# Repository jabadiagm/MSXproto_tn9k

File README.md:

# MSXproto_tn9k
Placa de prototipado para cartucho MSX y Tang Nano 9K

Placa de prototipo para conectar una Tang Nano 9K a una ranura de cartucho MSX. Se incluyen adaptadores de nivel de 5V a 3.3V para los pines de salida digitales del cartucho.

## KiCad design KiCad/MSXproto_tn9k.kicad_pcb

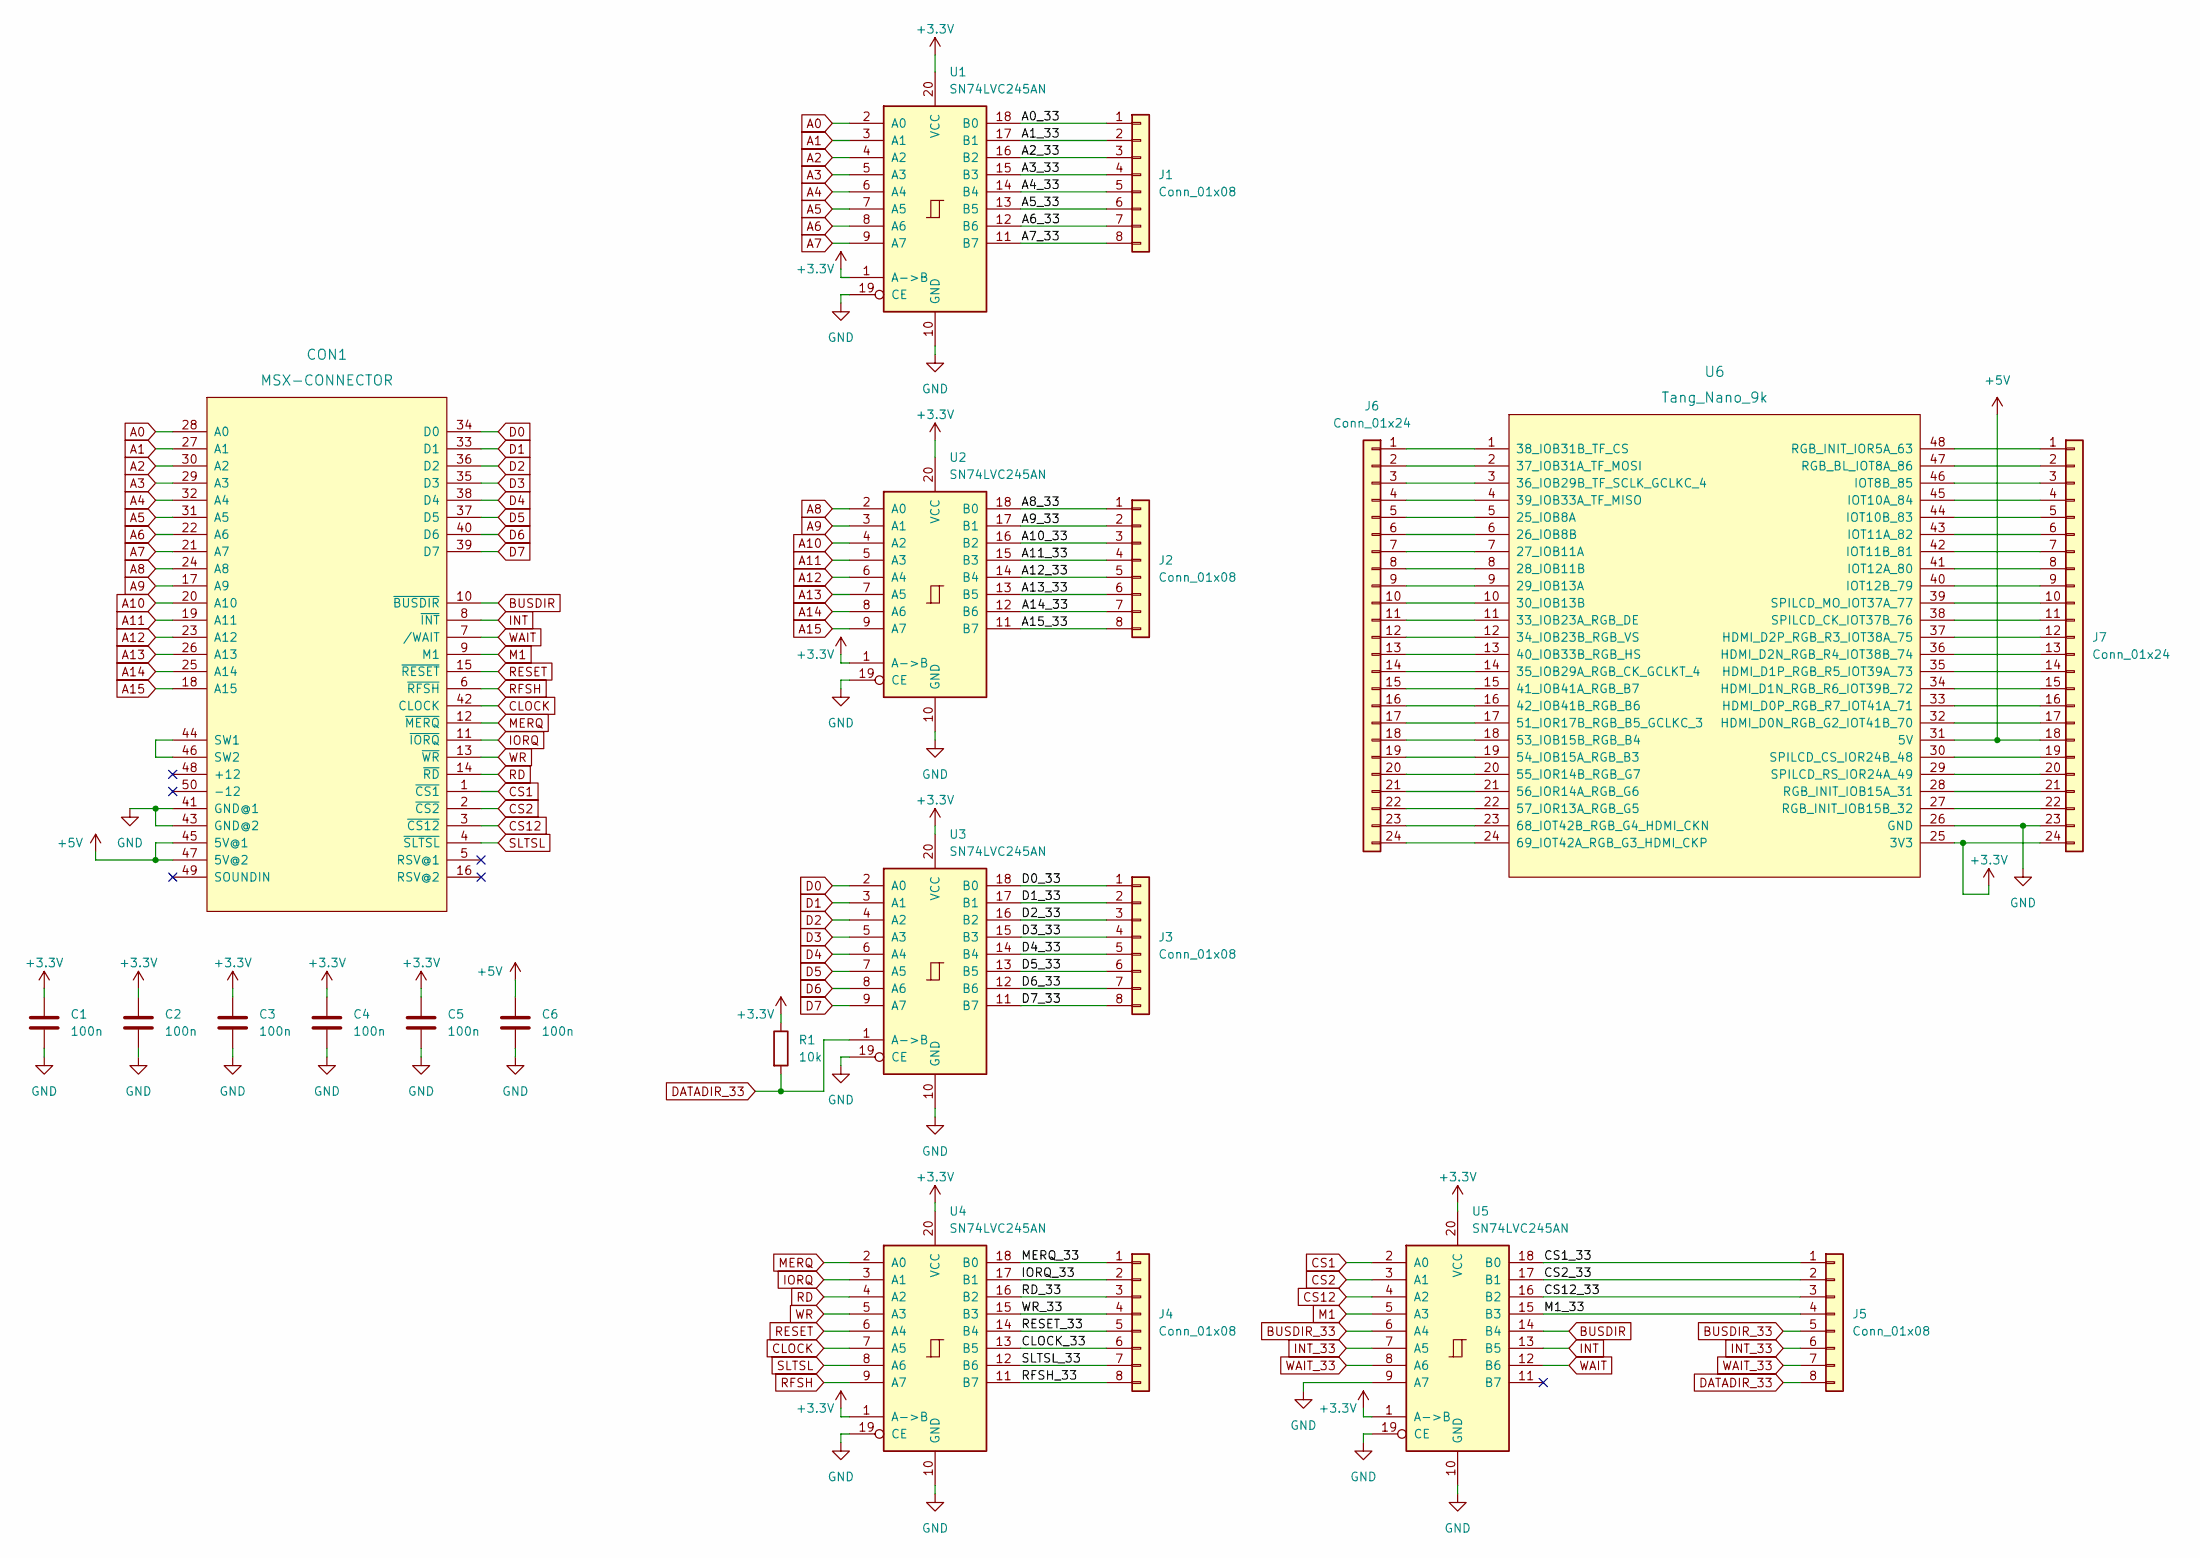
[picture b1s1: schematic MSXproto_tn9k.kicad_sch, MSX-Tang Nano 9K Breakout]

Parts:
C1, C2, C3, C4, C5, C6: 100n; C_Disc_D4.3mm_W1.9mm_P5.00mm
CON1: MSX-CONNECTOR; CARTRIDGE_MSX_XL
J1, J2, J3, J4, J5: Conn_01x08; PinSocket_1x08_P2.54mm_Vertical
J6, J7: Conn_01x24; PinSocket_1x24_P2.54mm_Vertical
R1: 10k; R_Axial_DIN0207_L6.3mm_D2.5mm_P7.62mm_Horizontal
U1, U2, U3, U4, U5: SN74LVC245AN; DIP-20_W7.62mm
U6: Tang_Nano_9k

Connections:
+3.3V: C1.1, C2.1, C3.1, C4.1, C5.1, J7.24, R1.1, U1.1 (A->B), U1.20 (VCC), U2.1 (A->B), U2.20 (VCC), U3.20 (VCC), U4.1 (A->B), U4.20 (VCC), U5.1 (A->B), U5.20 (VCC), U6.25 (3V3)
+5V: C6.1, CON1.45 (5V@1), CON1.47 (5V@2), J7.18, U6.31 (5V)
/A0_33: J1.1, U1.18 (B0)
/A1_33: J1.2, U1.17 (B1)
/A2_33: J1.3, U1.16 (B2)
/A3_33: J1.4, U1.15 (B3)
/A4_33: J1.5, U1.14 (B4)
/A5_33: J1.6, U1.13 (B5)
/A6_33: J1.7, U1.12 (B6)
/A7_33: J1.8, U1.11 (B7)
/A8_33: J2.1, U2.18 (B0)
/A9_33: J2.2, U2.17 (B1)
/A10_33: J2.3, U2.16 (B2)
/A11_33: J2.4, U2.15 (B3)
/A12_33: J2.5, U2.14 (B4)
/A13_33: J2.6, U2.13 (B5)
/A14_33: J2.7, U2.12 (B6)
/A15_33: J2.8, U2.11 (B7)
/CLOCK_33: J4.6, U4.13 (B5)
/CS1_33: J5.1, U5.18 (B0)
/CS2_33: J5.2, U5.17 (B1)
/CS12_33: J5.3, U5.16 (B2)
/D0_33: J3.1, U3.18 (B0)
/D1_33: J3.2, U3.17 (B1)
/D2_33: J3.3, U3.16 (B2)
/D3_33: J3.4, U3.15 (B3)
/D4_33: J3.5, U3.14 (B4)
/D5_33: J3.6, U3.13 (B5)
/D6_33: J3.7, U3.12 (B6)
/D7_33: J3.8, U3.11 (B7)
/IORQ_33: J4.2, U4.17 (B1)
/M1_33: J5.4, U5.15 (B3)
/MERQ_33: J4.1, U4.18 (B0)
/RD_33: J4.3, U4.16 (B2)
/RESET_33: J4.5, U4.14 (B4)
/RFSH_33: J4.8, U4.11 (B7)
/SLTSL_33: J4.7, U4.12 (B6)
/WR_33: J4.4, U4.15 (B3)
A0: CON1.28 (A0), U1.2 (A0)
A1: CON1.27 (A1), U1.3 (A1)
A2: CON1.30 (A2), U1.4 (A2)
A3: CON1.29 (A3), U1.5 (A3)
A4: CON1.32 (A4), U1.6 (A4)
A5: CON1.31 (A5), U1.7 (A5)
A6: CON1.22 (A6), U1.8 (A6)
A7: CON1.21 (A7), U1.9 (A7)
A8: CON1.24 (A8), U2.2 (A0)
A9: CON1.17 (A9), U2.3 (A1)
A10: CON1.20 (A10), U2.4 (A2)
A11: CON1.19 (A11), U2.5 (A3)
A12: CON1.23 (A12), U2.6 (A4)
A13: CON1.26 (A13), U2.7 (A5)
A14: CON1.25 (A14), U2.8 (A6)
A15: CON1.18 (A15), U2.9 (A7)
BUSDIR: CON1.10 (~BUSDIR), U5.14 (B4)
BUSDIR_33: J5.5, U5.6 (A4)
CLOCK: CON1.42 (CLOCK), U4.7 (A5)
CS1: CON1.1 (~CS1), U5.2 (A0)
CS2: CON1.2 (~CS2), U5.3 (A1)
CS12: CON1.3 (~CS12), U5.4 (A2)
D0: CON1.34 (D0), U3.2 (A0)
D1: CON1.33 (D1), U3.3 (A1)
D2: CON1.36 (D2), U3.4 (A2)
D3: CON1.35 (D3), U3.5 (A3)
D4: CON1.38 (D4), U3.6 (A4)
D5: CON1.37 (D5), U3.7 (A5)
D6: CON1.40 (D6), U3.8 (A6)
D7: CON1.39 (D7), U3.9 (A7)
DATADIR_33: J5.8, R1.2, U3.1 (A->B)
GND: C1.2, C2.2, C3.2, C4.2, C5.2, C6.2, CON1.41 (GND@1), CON1.43 (GND@2), J7.23, U1.10 (GND), U1.19 (CE), U2.10 (GND), U2.19 (CE), U3.10 (GND), U3.19 (CE), U4.10 (GND), U4.19 (CE), U5.9 (A7), U5.10 (GND), U5.19 (CE), U6.26 (GND)
INT: CON1.8 (~INT), U5.13 (B5)
INT_33: J5.6, U5.7 (A5)
IORQ: CON1.11 (~IORQ), U4.3 (A1)
M1: CON1.9 (M1), U5.5 (A3)
MERQ: CON1.12 (~MERQ), U4.2 (A0)
unnamed: CON1.44 (SW1), CON1.46 (SW2)
unnamed: J6.1, U6.1 (38_IOB31B_TF_CS)
unnamed: J6.2, U6.2 (37_IOB31A_TF_MOSI)
unnamed: J6.3, U6.3 (36_IOB29B_TF_SCLK_GCLKC_4)
unnamed: J6.4, U6.4 (39_IOB33A_TF_MISO)
unnamed: J6.5, U6.5 (25_IOB8A)
unnamed: J6.6, U6.6 (26_IOB8B)
unnamed: J6.7, U6.7 (27_IOB11A)
unnamed: J6.8, U6.8 (28_IOB11B)
unnamed: J6.9, U6.9 (29_IOB13A)
unnamed: J6.10, U6.10 (30_IOB13B)
unnamed: J6.11, U6.11 (33_IOB23A_RGB_DE)
unnamed: J6.12, U6.12 (34_IOB23B_RGB_VS)
unnamed: J6.13, U6.13 (40_IOB33B_RGB_HS)
unnamed: J6.14, U6.14 (35_IOB29A_RGB_CK_GCLKT_4)
unnamed: J6.15, U6.15 (41_IOB41A_RGB_B7)
unnamed: J6.16, U6.16 (42_IOB41B_RGB_B6)
unnamed: J6.17, U6.17 (51_IOR17B_RGB_B5_GCLKC_3)
unnamed: J6.18, U6.18 (53_IOB15B_RGB_B4)
unnamed: J6.19, U6.19 (54_IOB15A_RGB_B3)
unnamed: J6.20, U6.20 (55_IOR14B_RGB_G7)
unnamed: J6.21, U6.21 (56_IOR14A_RGB_G6)
unnamed: J6.22, U6.22 (57_IOR13A_RGB_G5)
unnamed: J6.23, U6.23 (68_IOT42B_RGB_G4_HDMI_CKN)
unnamed: J6.24, U6.24 (69_IOT42A_RGB_G3_HDMI_CKP)
unnamed: J7.22, U6.27 (RGB_INIT_IOB15B_32)
unnamed: J7.21, U6.28 (RGB_INIT_IOB15A_31)
unnamed: J7.20, U6.29 (SPILCD_RS_IOR24A_49)
unnamed: J7.19, U6.30 (SPILCD_CS_IOR24B_48)
unnamed: J7.17, U6.32 (HDMI_D0N_RGB_G2_IOT41B_70)
unnamed: J7.16, U6.33 (HDMI_D0P_RGB_R7_IOT41A_71)
unnamed: J7.15, U6.34 (HDMI_D1N_RGB_R6_IOT39B_72)
unnamed: J7.14, U6.35 (HDMI_D1P_RGB_R5_IOT39A_73)
unnamed: J7.13, U6.36 (HDMI_D2N_RGB_R4_IOT38B_74)
unnamed: J7.12, U6.37 (HDMI_D2P_RGB_R3_IOT38A_75)
unnamed: J7.11, U6.38 (SPILCD_CK_IOT37B_76)
unnamed: J7.10, U6.39 (SPILCD_MO_IOT37A_77)
unnamed: J7.9, U6.40 (IOT12B_79)
unnamed: J7.8, U6.41 (IOT12A_80)
unnamed: J7.7, U6.42 (IOT11B_81)
unnamed: J7.6, U6.43 (IOT11A_82)
unnamed: J7.5, U6.44 (IOT10B_83)
unnamed: J7.4, U6.45 (IOT10A_84)
unnamed: J7.3, U6.46 (IOT8B_85)
unnamed: J7.2, U6.47 (RGB_BL_IOT8A_86)
unnamed: J7.1, U6.48 (RGB_INIT_IOR5A_63)
RD: CON1.14 (~RD), U4.4 (A2)
RESET: CON1.15 (~RESET), U4.6 (A4)
RFSH: CON1.6 (~RFSH), U4.9 (A7)
SLTSL: CON1.4 (~SLTSL), U4.8 (A6)
WAIT: CON1.7 (/WAIT), U5.12 (B6)
WAIT_33: J5.7, U5.8 (A6)
WR: CON1.13 (~WR), U4.5 (A3)

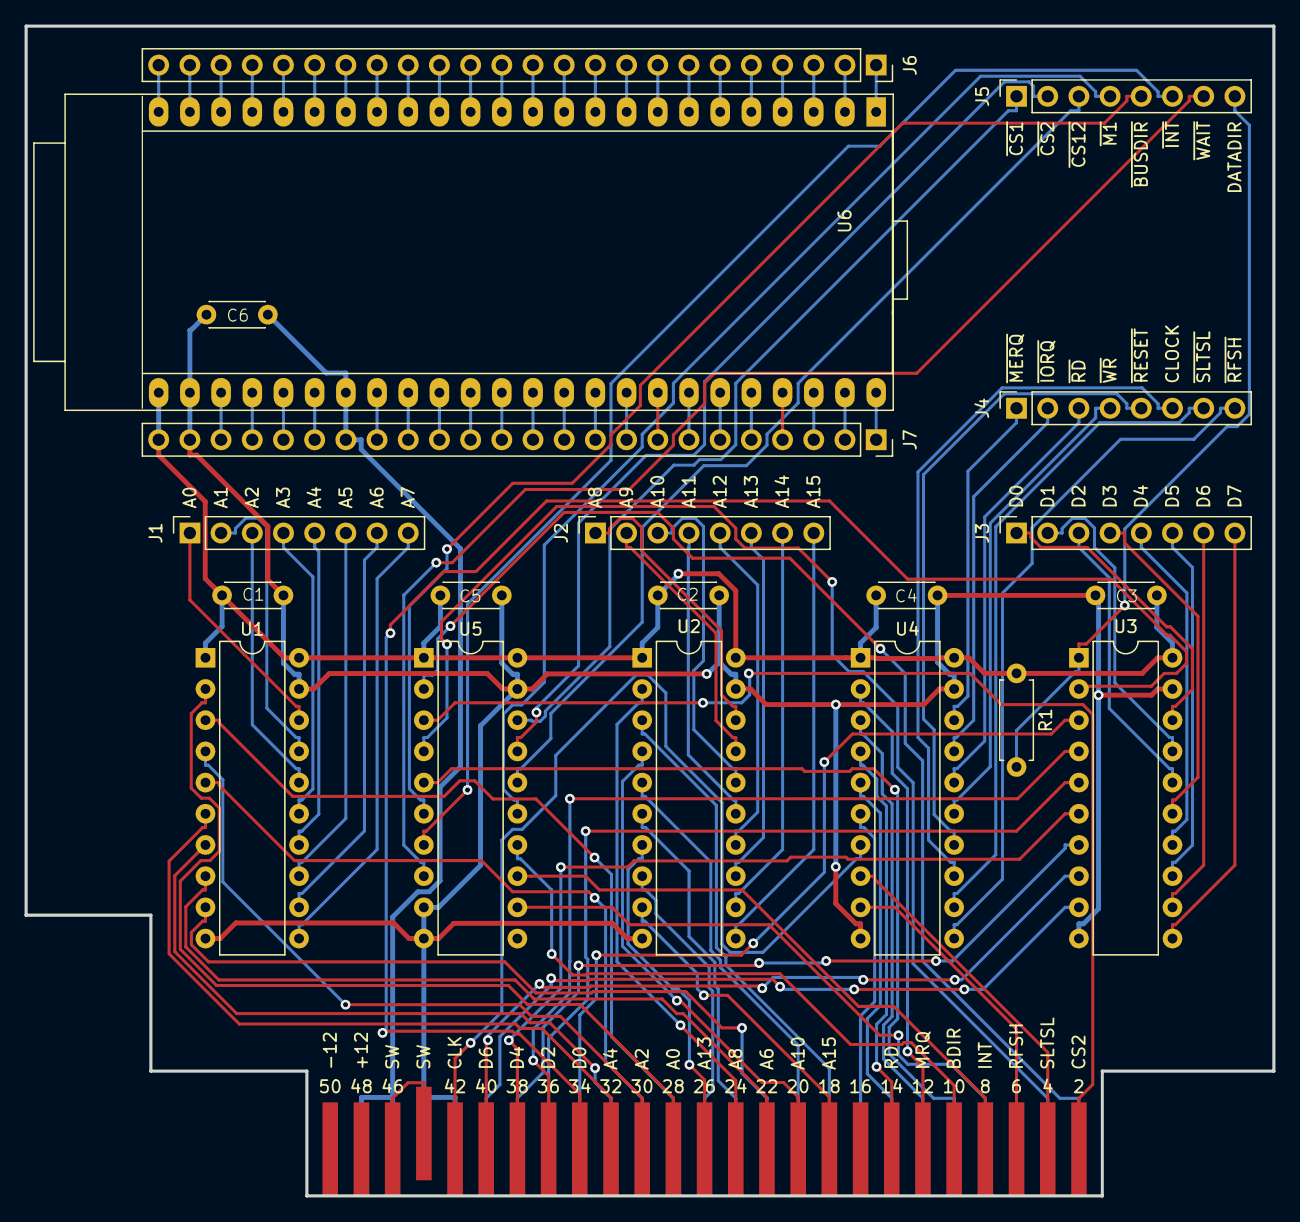
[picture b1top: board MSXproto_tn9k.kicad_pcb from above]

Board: 2 copper layers, 101.6 x 95.2 mm, 21 parts (0 on the bottom side), 128 nets.

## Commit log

2023-05-09 Inicial
